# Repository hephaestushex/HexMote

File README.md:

# HexMote
A wireless game controller with a built in IMU, allowing for motion controlled games. Uses the nRF52840 SuperMini and the ICM-20948 for motion controls.

# Inspiration
Recently, I started playing Mario Kart with my sister, but unfortunately for her, she's not too good at video games. The controllers I got, while having hall effect joysticks, lacked motion controls, so my poor sister struggled to steer with the tiny joystick, while turning the controller to no avail. So, I decided to make a Wii-mote-esque controller that would improve the usage while playing motion controlled games. That led birth to the HexMote, a wireless game controller built solely to improve less video-game inclined people.

# Schematic + PCB

Gerbers can be found in pcb/production

The schematic initially used a switch matrix, but falling back to direct pins proved better for pcb traces.

The PCB is 90x40mm, and has surfacemounted THT components through plugging holes with solder, and THT buttons and joysticks

# CAD

The case is split up into 3 parts, one of the top shell, one of the bottom shell, and one of the buttons all together

The PCB mounts on printed standoffs with heatset inserts placed within them, and the m3x6 screws directly into the top shell, through the pcb, and into the insert

# Firmware

The firmware for the hexmote is coded with Arduino, and uses several libraries to allow for BLE communication.

Unfortunately, there are no ways of directly parsing the gyro data within a game, so this requires a Cemuhook DSU script, which is included in the repo. Joystick and buttons work as normal however.

DISCLAIMER: As of right now, the code is AI generated and has not been tested on a physical product. Firmware will be updated and fixed once the HexMote has been built.

# BOM

| Item Name | Qty | Price (total) (USD) | Item link | Notes |
|---|---|---|---|---|
| nRF52840 ProMicro | 1 | $0.99 | [Link](https://www.aliexpress.com/item/1005007383270623.html) | Any nice!nano compatible board should work, check pcb footprint though |
| ICM-20948 Breakout Board | 1 | $4.20 | [Link](https://www.aliexpress.com/item/1005009307235033.html) | You can get a different IMU, but you have to code the sensor fusion code yourself |
| Right Angle Buttons | 2 | $0.99 | [Link](https://www.aliexpress.com/item/1005010093330224.html) | Make sure you get the right length (6x6x7) |
| JST-PH Connector | 1 | $0.99 | [Link](https://www.aliexpress.com/item/1005008970428474.html) | Make sure you get the right connector (right angle) |
| ALPS RKJXV Joystick | 1 | $0.99 | [Link](https://www.aliexpress.com/item/1005009112250803.html) | Make sure you get the PS4 style joystick |
| Soft Tactile Pushbutton | 8 | $0.99 | [Link](https://www.aliexpress.com/item/1005004588874318.html) | Do not substitute for regular clicky buttons, they are not the same footprint |
| M3x5x4 Inserts | 4 | $0.99 | [Link](https://www.aliexpress.com/item/1005011959188413.html) | Ships as 100 |
| M3x6 screws | 4 | $0.99 | [Link](https://www.aliexpress.com/item/32794842281.html) | Ships as 100 |
| 3.7v 500 mah lipo | 1 | $0.99 | [Link](https://www.aliexpress.com/item/1005001485127987) | Really anything works here so long as it meets the 5mm thick, up to 35mm by 80mm dimension requirement and has a jst ph 2.0 connector |
| PCB | 1 | $3.50 | [Link](https://github.com/hephaestushex/HexMote/blob/2a16dff57269423145945d0d09d0ee5307a6468b/pcb/production/hexmote_pcb.zip) | Link is to gerber files, JLC ships the total for 3.50 to Canada |
| Case | 1 | $1.00 | [Link](https://github.com/hephaestushex/HexMote/blob/d6d5b4342bca9d7315f2470e53cb6bb6a80dd431/cad/3d%20print.3mf) | Price differs based on filament. Bambu Lab PLA Matte is used here |
| **Total Price (USD):** | | **$16.62** | | |

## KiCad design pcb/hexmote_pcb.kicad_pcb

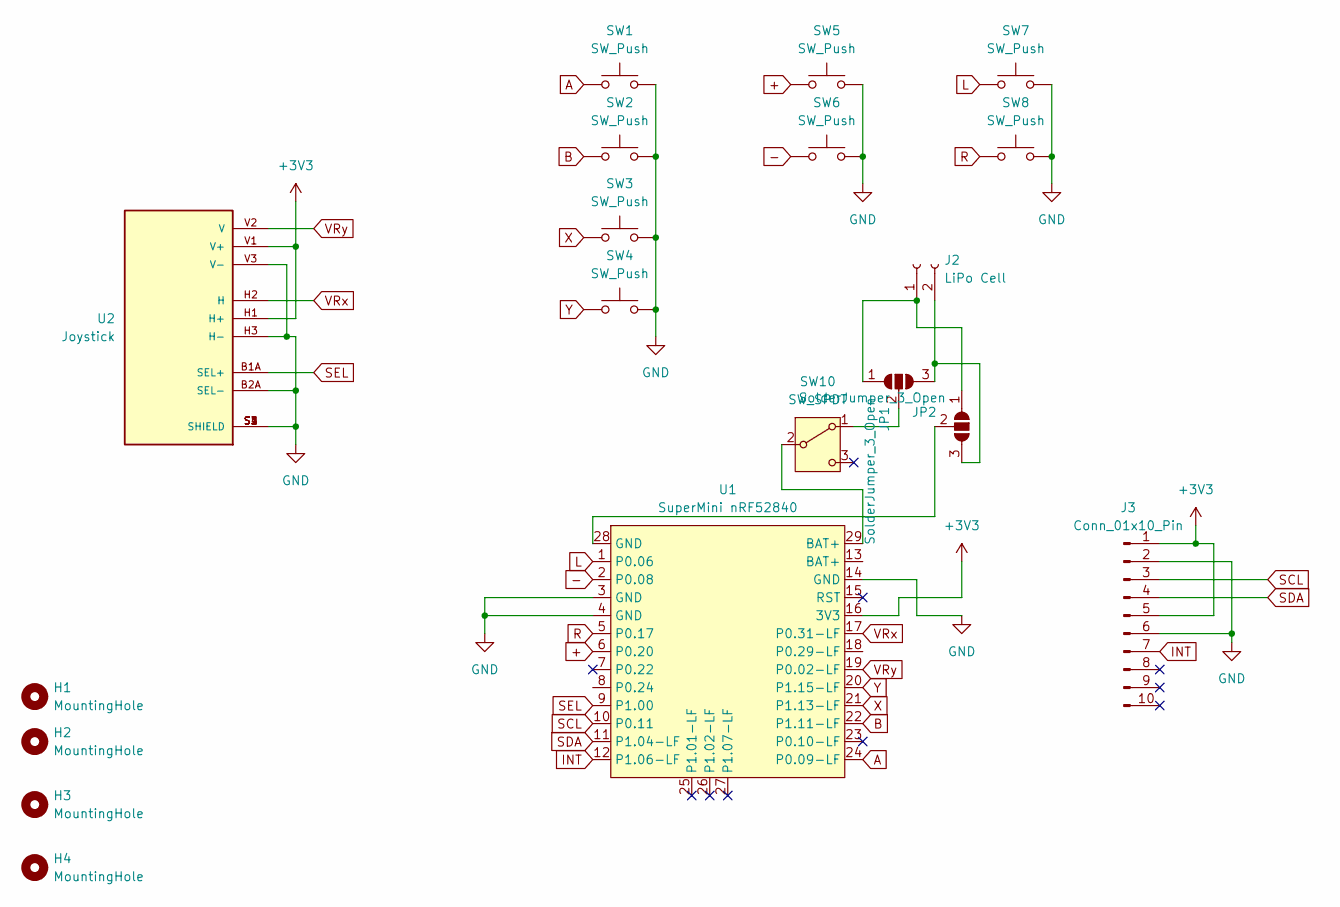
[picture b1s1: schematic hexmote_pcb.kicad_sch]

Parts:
H1, H2, H3, H4: MountingHole; MountingHole_3.2mm_M3
J2: LiPo Cell; JST_PH_S2B-PH-K_1x02_P2.00mm_Horizontal
J3: Conn_01x10_Pin; ICM-20498_Board
JP1, JP2: SolderJumper_3_Open; SolderJumper-3_P1.3mm_Open_Pad1.0x1.5mm_NumberLabels
SW1, SW2, SW3, SW4, SW5, SW6: SW_Push; Soft_Tactile_Button_6.00x4.5mm
SW7, SW8: SW_Push; SW_Tactile_SPST_Angled_PTS645Vx83-2LFS
SW10: SW_SPDT; SW_Slide_SPDT_Straight_CK_OS102011MS2Q
U1: SuperMini nRF52840; SuperMini NRF52840
U2: Joystick; PS4_joystick; PARTREV N/A

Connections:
+: SW5.1, U1.6 (P0.20)
+3V3: J3.1, J3.5, U1.16 (3V3), U2.H1 (H+), U2.V1 (V+)
-: SW6.1, U1.2 (P0.08)
A: SW1.1, U1.24 (P0.09-LF)
B: SW2.1, U1.22 (P1.11-LF)
GND: J3.2, J3.6, SW1.2, SW2.2, SW3.2, SW4.2, SW5.2, SW6.2, SW7.2, SW8.2, U1.3 (GND), U1.4 (GND), U1.14 (GND), U2.B2A (SEL-), U2.H3 (H-), U2.S1 (SHIELD), U2.S2 (SHIELD), U2.S3 (SHIELD), U2.S4 (SHIELD), U2.V3 (V-)
INT: J3.7, U1.12 (P1.06-LF)
L: SW7.1, U1.1 (P0.06)
unnamed: J2.1, JP1.1 (A), JP2.1 (A)
unnamed: J2.2, JP1.3 (B), JP2.3 (B)
unnamed: JP1.2 (C), SW10.1 (A)
unnamed: JP2.2 (C), U1.28 (GND)
unnamed: SW10.2 (B), U1.29 (BAT+)
R: SW8.1, U1.5 (P0.17)
SCL: J3.3, U1.10 (P0.11)
SDA: J3.4, U1.11 (P1.04-LF)
SEL: U1.9 (P1.00), U2.B1A (SEL+)
VRx: U1.17 (P0.31-LF), U2.H2 (H)
VRy: U1.19 (P0.02-LF), U2.V2 (V)
X: SW3.1, U1.21 (P1.13-LF)
Y: SW4.1, U1.20 (P1.15-LF)

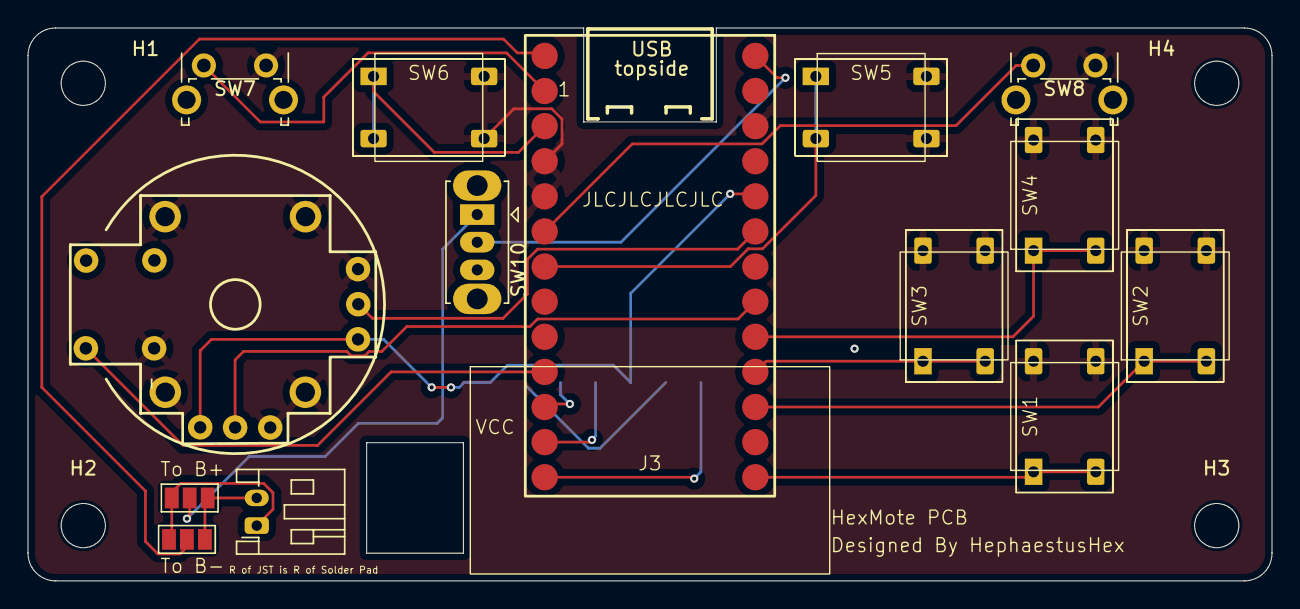
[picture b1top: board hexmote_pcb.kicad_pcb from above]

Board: 2 copper layers, 90.0 x 40.0 mm, 19 parts (0 on the bottom side), 21 nets.

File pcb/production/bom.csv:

Designator,Footprint,Quantity,Value,LCSC Part #
J2,JST_PH_S2B-PH-K_1x02_P2.00mm_Horizontal,1,LiPo Cell,
J3,ICM-20498_Board,1,Conn_01x10_Pin,
"SW1, SW2, SW3, SW4, SW5, SW6",Soft_Tactile_Button_6.00x4.5mm,6,SW_Push,
SW10,SW_Slide_SPDT_Straight_CK_OS102011MS2Q,1,SW_SPDT,
"SW7, SW8",SW_Tactile_SPST_Angled_PTS645Vx58-2LFS,2,SW_Push,
U2,PS4_joystick,1,Joystick,
